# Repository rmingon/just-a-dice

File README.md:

# Just a Dice

An electronic dice based on the CH32V003 RISC-V microcontroller with bottom-mounted switch activation.

## Overview

This project is a compact electronic dice that uses bottom-mounted switch buttons for activation. Simply press the PCB from the bottom to activate the switches and generate a random number displayed on 6 LEDs arranged in a traditional dice pattern.

## Schematic and PCB Layout

## Hardware Features

- **Microcontroller**: CH32V003F4P6 (RISC-V 32-bit)
- **Display**: 6 LEDs arranged in dice pattern (D1-D6)
- **Input**: 4 touch-sensitive pads on bottom (pad1-pad4)
- **Power**: Micro USB connector with onboard 3.3V regulation
- **Programming**: SWD interface with BOOT switch
- **Dimensions**: 45mm x 45mm PCB

## Components

- **U1**: CH32V003F4P6 microcontroller
- **U3**: AMS1117-3.3 voltage regulator
- **D1-D6**: LEDs for dice display
- **R5-R10**: Current limiting resistors for LEDs
- **J2**: Micro USB connector
- **J3**: SWD programming header
- **BOOT5**: Boot mode switch
- **C1-C4**: Decoupling capacitors

## How It Works

1. Power the device via micro USB
2. Press anywhere on the bottom of the PCB (touch pads)
3. The microcontroller generates a random number (1-6)
4. The corresponding LED pattern displays the result

## Programming

The CH32V003 can be programmed via the SWD interface using the onboard programming header (J3). Hold the BOOT switch while powering on to enter programming mode.

## License

This project is licensed under the CERN Open Hardware Licence Version 2 - Strongly Reciprocal (CERN-OHL-S).

## Files

- `hardware/`: KiCad PCB design files
- `schematic.png`: Circuit schematic
- `pcb.png`: PCB layout
- `3d_top.png`: 3D render of PCB top
- `3d_bottom.png`: 3D render of PCB bottom showing touch pads

## Getting Started

1. Assemble the PCB with all components
2. Program the CH32V003 with dice firmware
3. Connect via micro USB
4. Press the bottom to roll the dice!

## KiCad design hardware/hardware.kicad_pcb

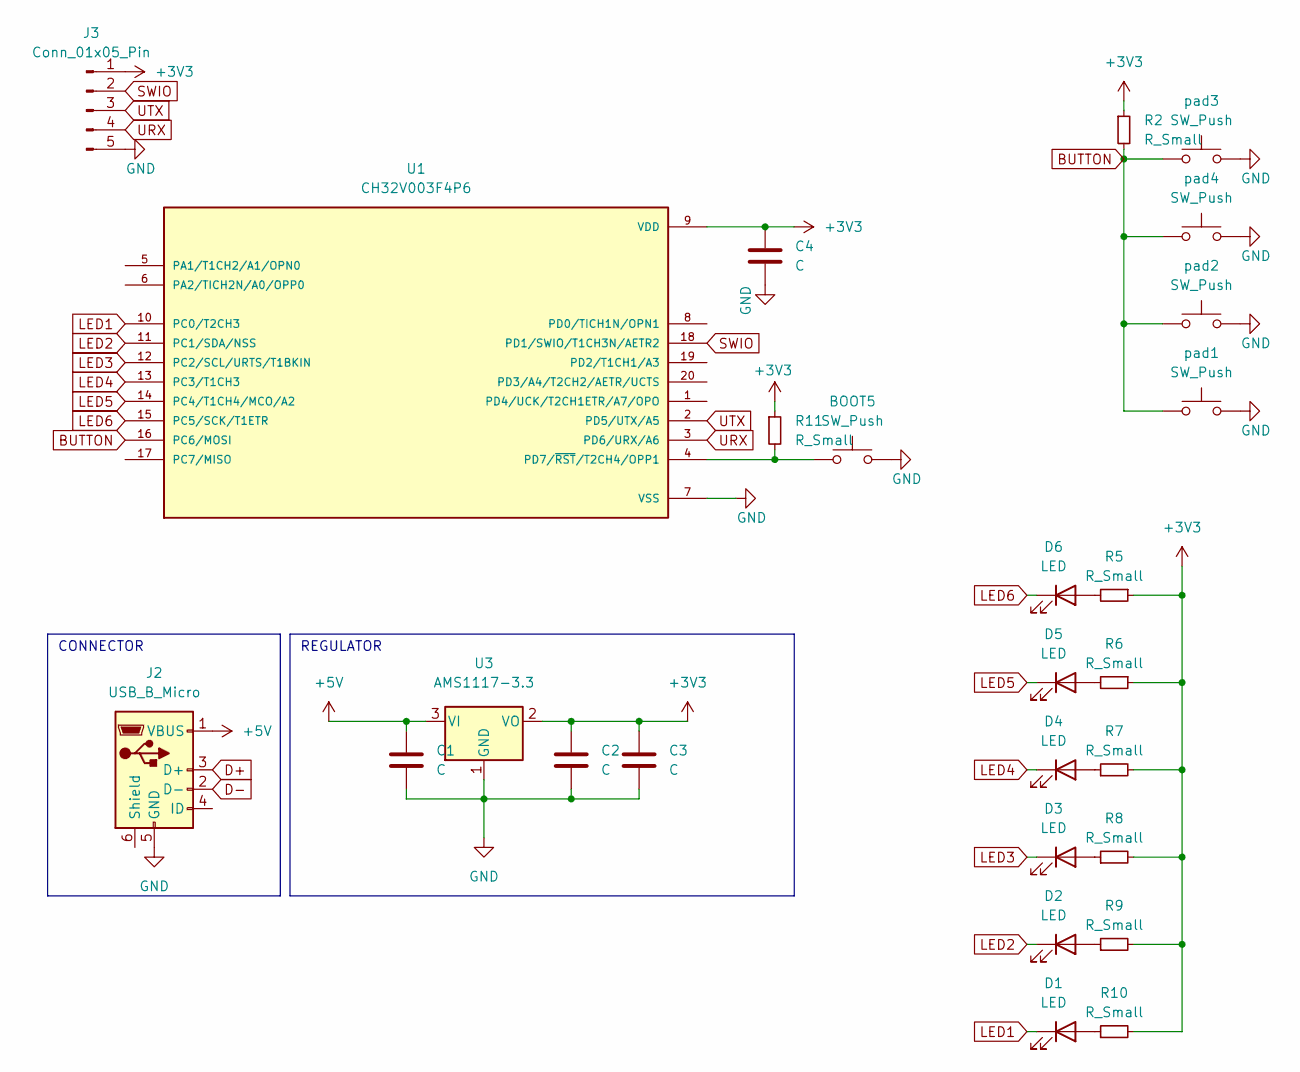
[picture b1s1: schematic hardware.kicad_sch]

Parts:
BOOT5: SW_Push; SW_SPST_FSMSM
C1, C2, C3, C4: C; C_0603_1608Metric
D1, D2, D3, D4, D5, D6: LED; LED_0603_1608Metric
J2: USB_B_Micro; USB_Micro-B_Amphenol_10118194_Horizontal
J3: Conn_01x05_Pin; PinSocket_1x05_P2.54mm_Horizontal
R2, R5, R6, R7, R8, R9, R10, R11: R_Small; R_0603_1608Metric
U1: CH32V003F4P6; SOP65P640X121-20N; PARTREV 1.4
U3: AMS1117-3.3; SOT-223-3_TabPin2
pad1, pad2, pad3, pad4: SW_Push; SW_SPST_FSMSM

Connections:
+3V3: C2.1, C3.1, C4.1, J3.1, R2.1, R5.1, R6.1, R7.2, R8.2, R9.2, R10.2, R11.1, U1.9 (VDD), U3.2 (VO)
+5V: C1.1, J2.1 (VBUS), U3.3 (VI)
BUTTON: R2.2, U1.16 (PC6/MOSI), pad1.1, pad2.1, pad3.1, pad4.1
D+: J2.3 (D+)
D-: J2.2 (D-)
GND: BOOT5.2, C1.2, C2.2, C3.2, C4.2, J2.5 (GND), J3.5, U1.7 (VSS), U3.1 (GND), pad1.2, pad2.2, pad3.2, pad4.2
LED1: D1.1 (K), U1.10 (PC0/T2CH3)
LED2: D2.1 (K), U1.11 (PC1/SDA/NSS)
LED3: D3.1 (K), U1.12 (PC2/SCL/URTS/T1BKIN)
LED4: D4.1 (K), U1.13 (PC3/T1CH3)
LED5: D5.1 (K), U1.14 (PC4/T1CH4/MCO/A2)
LED6: D6.1 (K), U1.15 (PC5/SCK/T1ETR)
unnamed: D1.2 (A), R10.1
unnamed: D2.2 (A), R9.1
unnamed: D3.2 (A), R8.1
unnamed: D4.2 (A), R7.1
unnamed: D5.2 (A), R6.2
unnamed: D6.2 (A), R5.2
unnamed: BOOT5.1, R11.2, U1.4 (PD7/~RST/T2CH4/OPP1)
SWIO: J3.2, U1.18 (PD1/SWIO/T1CH3N/AETR2)
URX: J3.4, U1.3 (PD6/URX/A6)
UTX: J3.3, U1.2 (PD5/UTX/A5)

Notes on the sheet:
CONNECTOR
REGULATOR

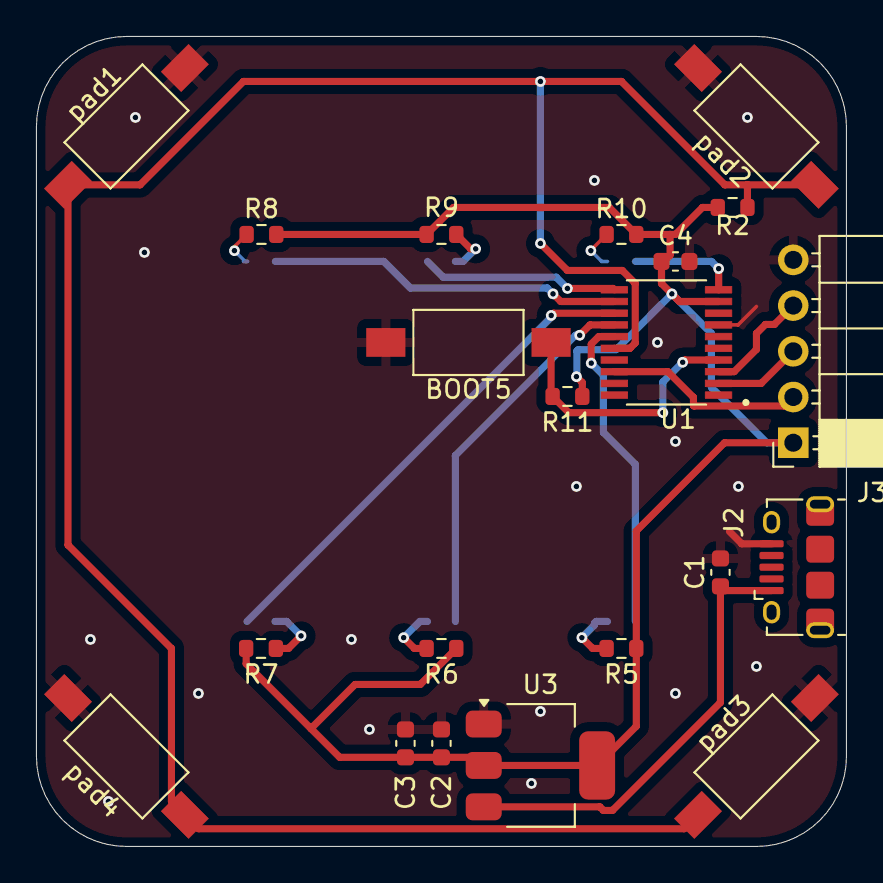
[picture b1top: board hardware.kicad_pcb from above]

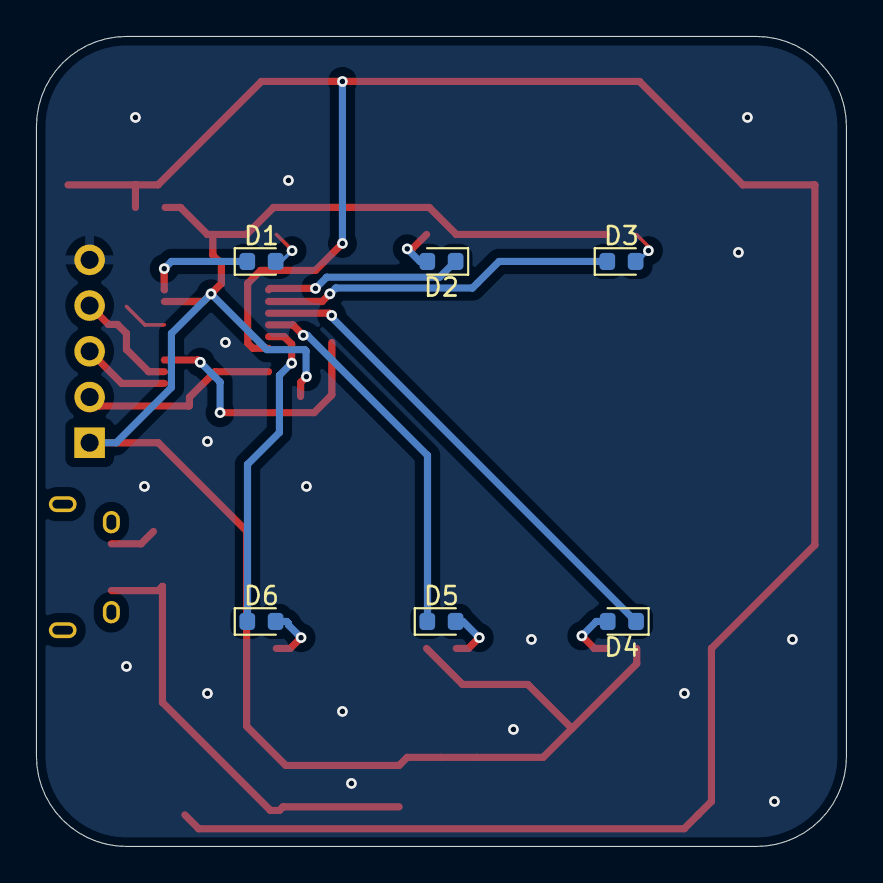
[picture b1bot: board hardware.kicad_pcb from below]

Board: 2 copper layers, 45.0 x 45.0 mm, 27 parts (6 on the bottom side), 20 nets.

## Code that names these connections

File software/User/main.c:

#include "debug.h"
#include "ch32v00x.h"
#include "ch32v00x_gpio.h"
#include "ch32v00x_rcc.h"

// LED pin definitions (PC0-PC5)
#define LED_PORT GPIOC
#define LED0_PIN GPIO_Pin_0
#define LED1_PIN GPIO_Pin_1
#define LED2_PIN GPIO_Pin_2
#define LED3_PIN GPIO_Pin_3
#define LED4_PIN GPIO_Pin_4
#define LED5_PIN GPIO_Pin_5

// Button pin definition (PC6)
#define BUTTON_PORT GPIOC
#define BUTTON_PIN GPIO_Pin_6

// Dice patterns for LEDs (6 LEDs can represent dice faces 1-6)
// Alternative dice patterns (more dice-like representation)
const uint8_t dice_patterns[7] = {
    0b000000,  // 0 - Not used
    0b000100,  // 1 - Center LED (LED2)
    0b001001,  // 2 - LED0 and LED3
    0b001101,  // 3 - LED0, LED2, LED3
    0b011011,  // 4 - LED0, LED1, LED3, LED4
    0b011111,  // 5 - LED0, LED1, LED2, LED3, LED4
    0b111111   // 6 - All LEDs
};

// Global variables
volatile uint32_t delay_counter = 0;

// Function prototypes
void GPIO_Configuration(void);
void Display_Dice(uint8_t number);
void Clear_LEDs(void);
uint8_t Generate_Random_Dice(void);
void Simple_Delay_ms(uint32_t ms);
void Dice_Animation(void);

// GPIO Configuration
void GPIO_Configuration(void)
{
    GPIO_InitTypeDef GPIO_InitStructure = {0};
    
    // Enable GPIOC clock
    RCC_PB2PeriphClockCmd(RCC_PB2Periph_GPIOC, ENABLE);
    
    // Configure PC0-PC5 as output push-pull for LEDs (inverted logic)
    GPIO_InitStructure.GPIO_Pin = LED0_PIN | LED1_PIN | LED2_PIN | 
                                  LED3_PIN | LED4_PIN | LED5_PIN;
    GPIO_InitStructure.GPIO_Mode = GPIO_Mode_Out_PP;
    GPIO_InitStructure.GPIO_Speed = GPIO_Speed_30MHz;
    GPIO_Init(LED_PORT, &GPIO_InitStructure);
    
    // Configure PC6 as input with pull-up for button
    GPIO_InitStructure.GPIO_Pin = BUTTON_PIN;
    GPIO_InitStructure.GPIO_Mode = GPIO_Mode_IPU;
    GPIO_Init(BUTTON_PORT, &GPIO_InitStructure);
    
    // Initialize all LEDs as OFF (HIGH for common cathode)
    Clear_LEDs();
}

// Clear all LEDs (turn OFF - set HIGH for common cathode)
void Clear_LEDs(void)
{
    GPIO_SetBits(LED_PORT, LED0_PIN | LED1_PIN | LED2_PIN | 
                 LED3_PIN | LED4_PIN | LED5_PIN);
}

// Display dice number on LEDs (inverted logic for common cathode)
void Display_Dice(uint8_t number)
{
    if (number < 1 || number > 6) return;
    
    Clear_LEDs(); // Turn all LEDs OFF (HIGH)
    
    uint8_t pattern = dice_patterns[number];
    
    // Turn ON LEDs by setting pins LOW
    if (pattern & 0x01) GPIO_ResetBits(LED_PORT, LED0_PIN);
    if (pattern & 0x02) GPIO_ResetBits(LED_PORT, LED1_PIN);
    if (pattern & 0x04) GPIO_ResetBits(LED_PORT, LED2_PIN);
    if (pattern & 0x08) GPIO_ResetBits(LED_PORT, LED3_PIN);
    if (pattern & 0x10) GPIO_ResetBits(LED_PORT, LED4_PIN);
    if (pattern & 0x20) GPIO_ResetBits(LED_PORT, LED5_PIN);
}

// Simple delay function (blocking)
void Simple_Delay_ms(uint32_t ms)
{
    // Rough delay for 24MHz clock
    for (uint32_t i = 0; i < ms; i++) {
        for (volatile uint32_t j = 0; j < 6000; j++) {
            delay_counter++; // Add randomness to the counter
        }
    }
}

// Generate random dice number (1-6)
uint8_t Generate_Random_Dice(void)
{
    // Simple pseudo-random using delay counter
    static uint32_t seed = 0xACE1;
    
    // Mix in the delay counter for randomness
    seed ^= delay_counter;
    seed = (seed * 1103515245 + 12345) & 0x7FFFFFFF;
    
    return (seed % 6) + 1;
}

// Dice rolling animation
void Dice_Animation(void)
{
    const uint8_t animation_cycles = 15;
    const uint32_t animation_delay = 80; // ms between changes
    
    for (uint8_t i = 0; i < animation_cycles; i++) {
        uint8_t random_num = Generate_Random_Dice();
        Display_Dice(random_num);
        Simple_Delay_ms(animation_delay);
    }
}

// Main function
int main(void)
{
    SystemCoreClockUpdate();
    
    // Initialize USART for debugging (optional)
    USART_Printf_Init(115200);
    printf("CH32V006 Dice Application Started (24MHz HSI)\r\n");
    
    // Configure GPIO
    GPIO_Configuration();
    
    // LED test sequence to verify all LEDs work
    printf("Testing all LEDs...\r\n");
    for (uint8_t i = 1; i <= 6; i++) {
        printf("Testing dice face: %d\r\n", i);
        Display_Dice(i);
        Simple_Delay_ms(500);
    }
    
    // Initial display - show "1"
    Display_Dice(1);
    
    printf("Press button on PC6 to roll the dice!\r\n");
    printf("Button: PC6 → Button → GND (with pull-up)\r\n");
    
    uint8_t last_button_state = 1;  // Button not pressed initially
    
    while(1)
    {
        // Read button state directly
        uint8_t button_state = GPIO_ReadInputDataBit(BUTTON_PORT, BUTTON_PIN);
        
        // Detect button press (transition from HIGH to LOW)
        if (last_button_state == 1 && button_state == 0) {
            printf("Button pressed! Rolling dice...\r\n");
            
            // Simple debounce delay
            Simple_Delay_ms(50);
            
            // Play dice animation
            Dice_Animation();
            
            // Generate final random number
            uint8_t dice_result = Generate_Random_Dice();
            
            // Display result
            Display_Dice(dice_result);
            
            printf("Dice result: %d\r\n", dice_result);
            
            // Wait for button release to prevent multiple triggers
            while (GPIO_ReadInputDataBit(BUTTON_PORT, BUTTON_PIN) == 0) {
                Simple_Delay_ms(10);
            }
            
            // Additional delay after release
            Simple_Delay_ms(200);
        }
        
        last_button_state = button_state;
        
        // Small delay in main loop to add randomness
        Simple_Delay_ms(1);
    }
}

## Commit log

2025-07-07 add pcb + schematic with wiring
2025-07-07 add 3D models and schematic images
2025-07-07 add initial README.md with project overview and details
2025-07-07 update README.md to include schematic and PCB layout images
2025-07-07 fix button
2025-07-07 fix mcu ground issue
2025-07-20 add code
